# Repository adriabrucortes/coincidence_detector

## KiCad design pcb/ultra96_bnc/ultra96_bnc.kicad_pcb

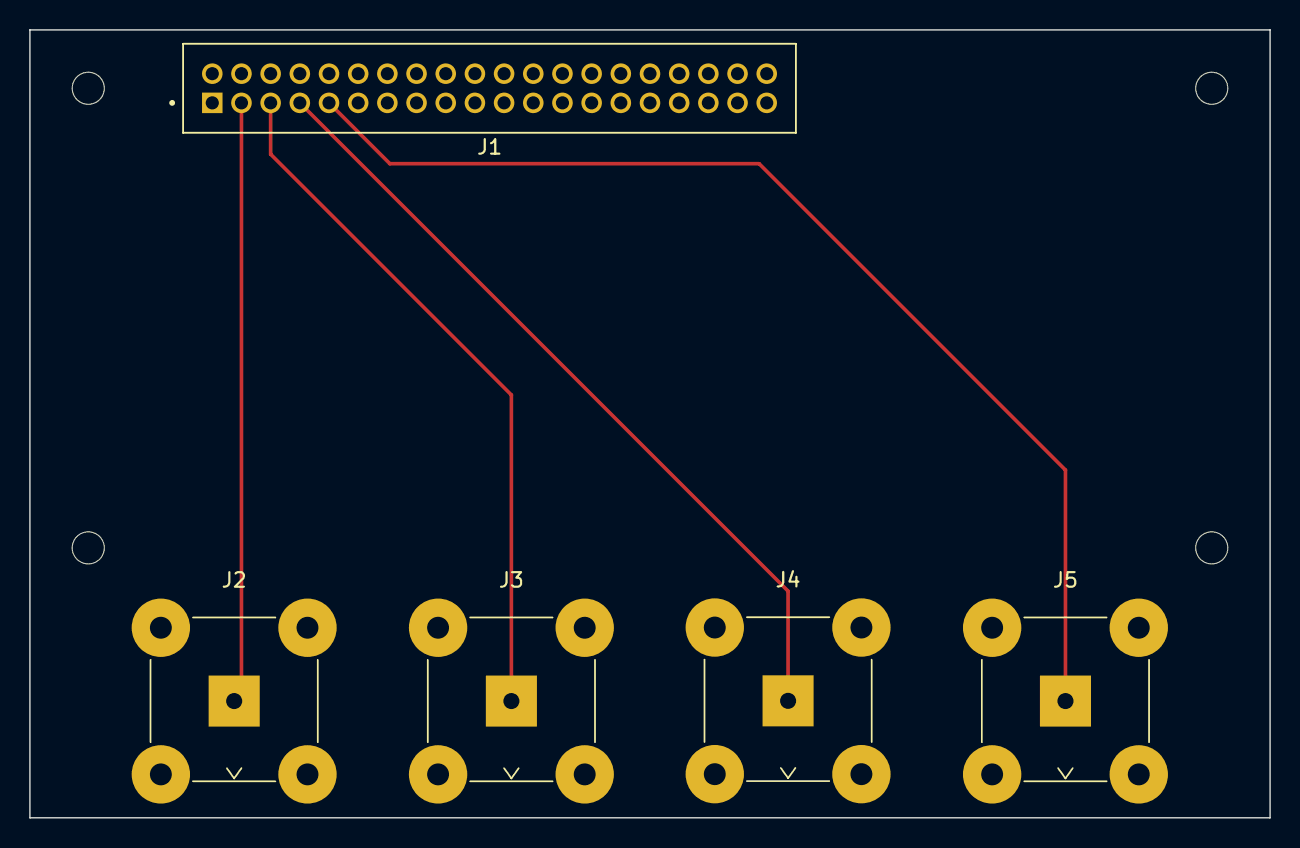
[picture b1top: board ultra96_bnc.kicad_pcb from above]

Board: 2 copper layers, 85.0 x 54.0 mm, 5 parts (0 on the bottom side), 6 nets.

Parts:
J1: 98414-G06-40ULF; AMPHENOL_98414-G06-40ULF
J2, J3, J4, J5: Conn_Coaxial; BNC_TEConnectivity_1478035_Horizontal

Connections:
GND: J1.A01, J1.A20, J1.B01, J1.B20, J2.2 (Ext), J3.2 (Ext), J4.2 (Ext), J5.2 (Ext)
HD_GPIO_0: J1.A02, J2.1 (In)
HD_GPIO_1: J1.A03, J3.1 (In)
HD_GPIO_2: J1.A04, J4.1 (In)
HD_GPIO_3: J1.A05, J5.1 (In)
VSYS_IN: J1.B18, J1.B19

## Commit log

2024-05-07 ja tenim disseny amics
2024-05-07 donete?
2024-05-08 reparacions i sembla que funciona :)
2024-05-08 moltes simplificacions
2024-05-12 cositas
2024-05-12 eliminar antic
2024-05-12 some things are working now, at least
2024-05-13 semifuncional :)
2024-05-15 working fine casi tutto
2024-07-04 Mogollon de coses
2024-07-04 canviar a 1.5GHz
